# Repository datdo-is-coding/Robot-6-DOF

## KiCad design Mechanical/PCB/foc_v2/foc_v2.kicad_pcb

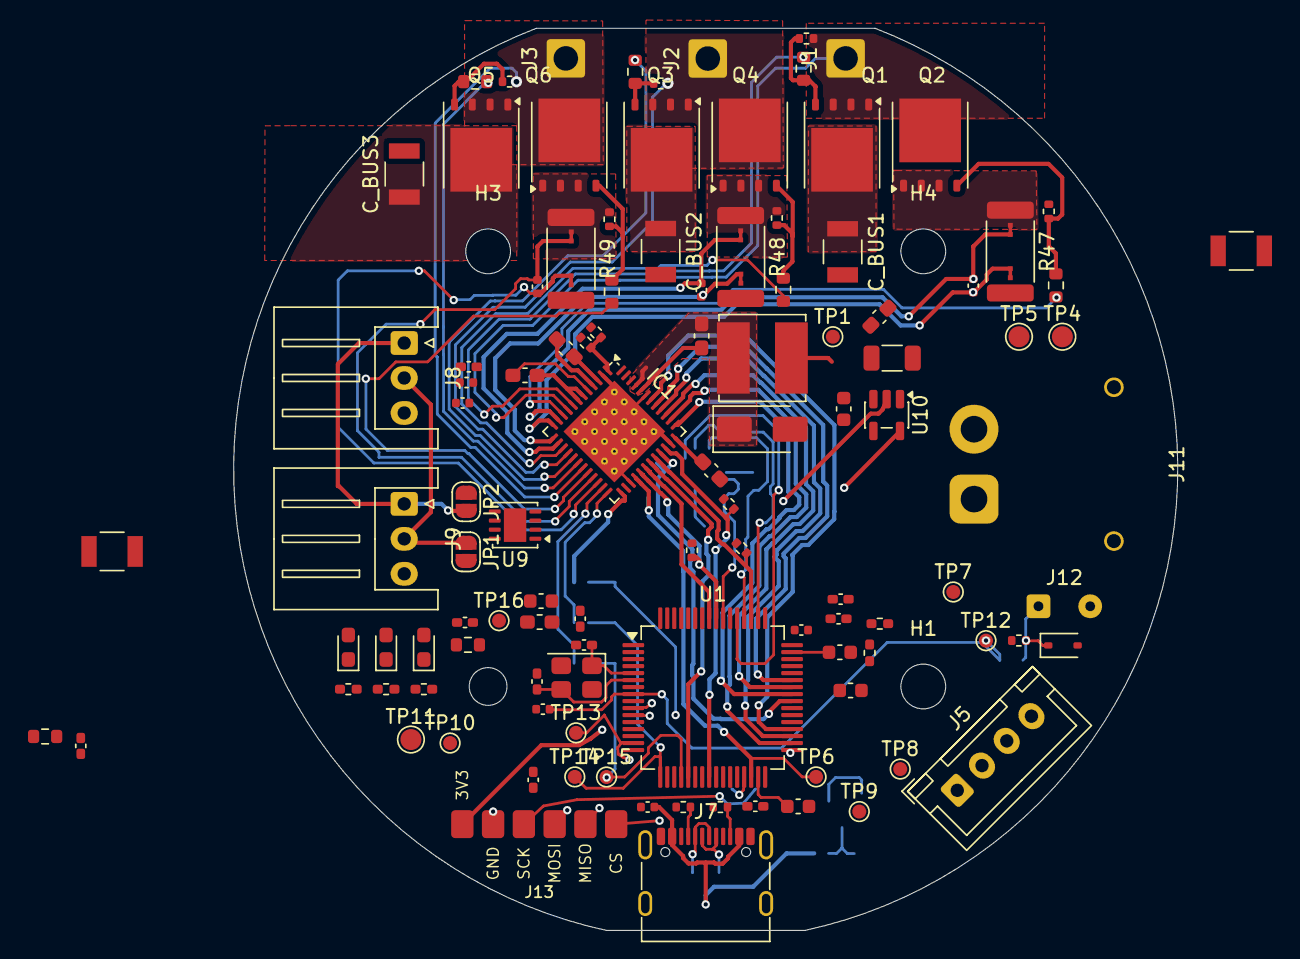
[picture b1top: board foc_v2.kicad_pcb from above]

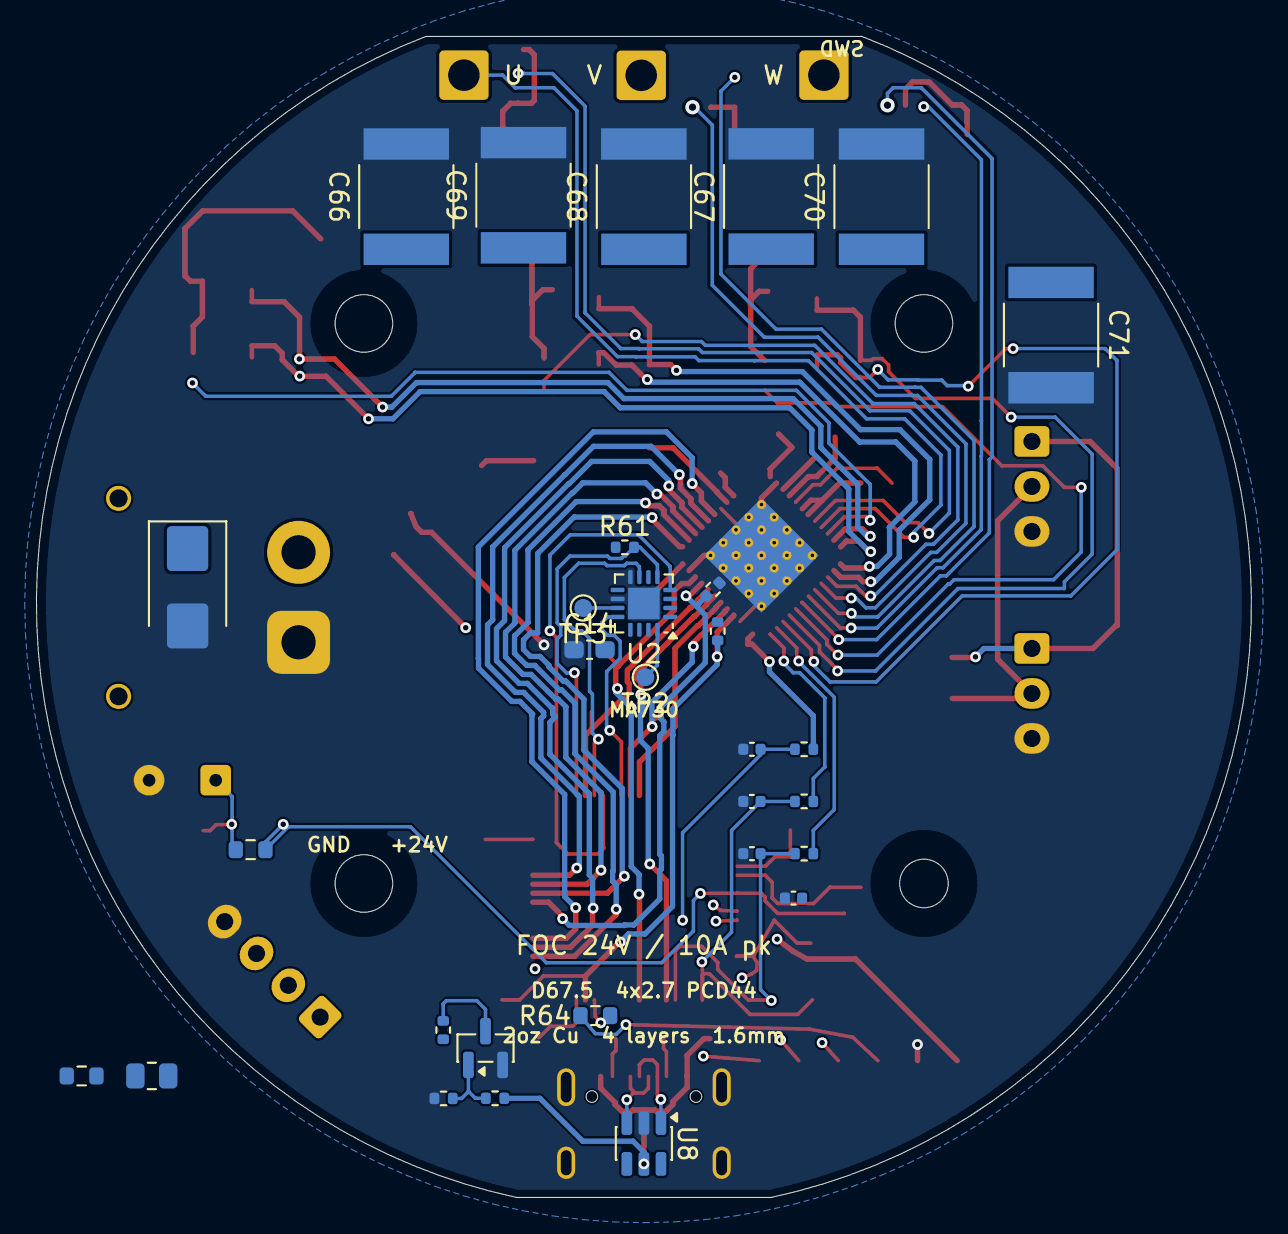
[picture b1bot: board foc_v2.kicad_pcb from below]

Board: 4 copper layers, 67.5 x 64.5 mm, 148 parts (30 on the bottom side), 98 nets.

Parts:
C1, C2, C3, C54, C55, C56: 1nF; C_0402_1005Metric
C4, C5, C7, C21, C50, C51, C52: 100nF; C_0402_1005Metric_Pad0.74x0.62mm_HandSolder
C6: 1uF; C_0402_1005Metric_Pad0.74x0.62mm_HandSolder
C8, C9: 33pF; C_0402_1005Metric_Pad0.74x0.62mm_HandSolder
C10, C11: 2.2uF; C_0603_1608Metric
C12, C17: 10uF; C_TDK_CGA6_SoftTerm_1210
C13, C15: 0.1uF; C_0603_1608Metric_Pad1.08x0.95mm_HandSolder
C14, C18, C20: 1uF; C_0603_1608Metric_Pad1.08x0.95mm_HandSolder
C16: 22uF; C_1206_3216Metric
C19: 47nF; C_0603_1608Metric_Pad1.08x0.95mm_HandSolder
C53, C59, C60, C61, C65: 100nF; C_0402_1005Metric
C57: 1uF; C_0603_1608Metric
C58: 4.7uF; C_0603_1608Metric
C62: 4.7nF; C_0603_1608Metric
C64: 10nF; C_0402_1005Metric
C66, C67, C68, C69, C70, C71: 22uF; C_TDK_CKG57N_6.0x5.0mm
C_BUS1, C_BUS2, C_BUS3: 10uF; C_TDK_CGA6_SoftTerm_1210
D1, D2: LED RED; LED_0603_1608Metric_Pad1.05x0.95mm_HandSolder
D3: LED GREEN; LED_0603_1608Metric_Pad1.05x0.95mm_HandSolder
D4: SS16; D_SMA
D6: SMBJ30A; D_SMB
D7: PESD3V3U1UA; D_SOD-323
FB1: 600R@100MHz; L_0603_1608Metric_Pad1.05x0.95mm_HandSolder
H1, H3, H4: MountingHole; MountingHole_3.2mm_M3
H2: MountingHole; MountingHole_2.7mm_M2.5
IC1: DRV8323RSRGZR; Texas_RGZ0048A_VQFN-48-1EP_7x7mm_P0.5mm_EP5.15x5.15mm_Therm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
J1: PHASE_U; SolderWire-1sqmm_1x01_D1.4mm_OD2.7mm
J2: PHASE_V; SolderWire-1sqmm_1x01_D1.4mm_OD2.7mm
J3: PHASE_W; SolderWire-1sqmm_1x01_D1.4mm_OD2.7mm
J5: Debug; JST_XH_B4B-XH-A_1x04_P2.50mm_Vertical
J7: USB_C_Receptacle_USB2.0_16P; USB_C_Receptacle_G-Switch_GT-USB-7010ASV
J8: CAN1; JST_XH_S3B-XH-A_1x03_P2.50mm_Horizontal
J9: CAN2; JST_XH_S3B-XH-A_1x03_P2.50mm_Horizontal
J11: 24V_IN; AMASS_XT30PW-M_Edge_NoSilk
J12: MOTOR_NTC; SolderWire-0.127sqmm_1x02_P3.7mm_D0.48mm_OD1mm
J13: ENC2; Encoder_SPI_SolderPads_1x06_P2.20mm
JP1: TERM_L; SolderJumper-2_P1.3mm_Open_RoundedPad1.0x1.5mm
JP2: TERM_H; SolderJumper-2_P1.3mm_Open_RoundedPad1.0x1.5mm
L1: 22uH; L_Bourns_SRN6045TA
NT1: KELVIN_CSA_SPA; NetTie_Kelvin
NT2: KELVIN_SNA; NetTie_Kelvin
NT3: KELVIN_CSA_SPB; NetTie_Kelvin
NT4: KELVIN_SNB; NetTie_Kelvin
NT5: KELVIN_CSA_SPC; NetTie_Kelvin
NT6: KELVIN_SNC; NetTie_Kelvin
Q1, Q2, Q3, Q4, Q5, Q6: CSD18532Q5B; TDSON-8-1
Q7: 2N7002; SOT-23
R1, R2, R3, R4, R5, R7: 2.2R; R_0603_1608Metric
R6: 18k; R_0402_1005Metric
R8, R42, R43, R52, R61, R62: 10k; R_0402_1005Metric
R9: 3k3; R_0402_1005Metric
R10, R50, R55, R56, R57, R58, R59, R60: 100k; R_0402_1005Metric
R32, R34: 10k; R_0402_1005Metric_Pad0.72x0.64mm_HandSolder
R33, R35, R36: 1k; R_0402_1005Metric_Pad0.72x0.64mm_HandSolder
R37, R38, R39: 100R; R_0402_1005Metric
R40, R41: 5.1k; R_0402_1005Metric
R44: 1M; R_0402_1005Metric
R45, R46: 60.4R; R_0603_1608Metric
R47, R48, R49: 5m; R_2512_6332Metric
R51: 4.7k; R_0402_1005Metric
R53: 150k; R_0805_2012Metric
R54: 10k; R_0603_1608Metric
R63: 1k; R_0603_1608Metric
R64: 33R; R_0603_1608Metric
TP1: TestPoint; TestPoint_Pad_D1.0mm
TP2: MGH_TP; TestPoint_Pad_D1.0mm
TP3: MGL_TP; TestPoint_Pad_D1.0mm
TP4: VS_24V; TestPoint_Pad_D1.5mm
TP5: PGND; TestPoint_Pad_D1.5mm
TP6: nFAULT; TestPoint_Pad_D1.0mm
TP7: ENABLE; TestPoint_Pad_D1.0mm
TP8: PV_SENSE; TestPoint_Pad_D1.0mm
TP9: +3V3; TestPoint_Pad_D1.0mm
TP10: +3V3A; TestPoint_Pad_D1.0mm
TP11: GND; TestPoint_Pad_D1.5mm
TP12: MOTOR_TEMP_ADC; TestPoint_Pad_D1.0mm
TP13: ADC_IA; TestPoint_Pad_D1.0mm
TP14: ADC_IB; TestPoint_Pad_D1.0mm
TP15: ADC_IC; TestPoint_Pad_D1.0mm
TP16: NRST; TestPoint_Pad_D1.0mm
U1: STM32F405RGTx; LQFP-64_10x10mm_P0.5mm
U2: MA730; MA730_QFN16_3x3
U8: USBLC6-2SC6; SOT-23-6
U9: TJA1051TK-3; HVSON-8-1EP_3x3mm_P0.65mm_EP1.6x2.4mm
U10: AP2112K-3.3; SOT-23-5
Y1: 12MHz; Crystal_SMD_3225-4Pin_3.2x2.5mm

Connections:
+3V3: C4.1, C14.2, C21.2, C50.1, C51.1, C52.1, C53.1, C58.1, C60.1, FB1.2, IC1.26 (VREF), J5.1, J13.1, R8.1, R32.1, R33.1, R35.1, R36.1, R42.1, R51.1, R52.1, R61.1, TP9.1 (1_1), U1.1 (VBAT), U1.19 (VDD), U1.32 (VDD), U1.48 (VDD), U1.64 (VDD), U2.13 (VDD), U9.5 (VIO), U10.5 (VOUT)
+3V3A: C5.1, C6.1, FB1.1, R62.1, TP10.1 (1_1), U1.13 (VDDA)
+5V: C16.1, C57.1, C61.1, L1.1, R6.1, TP1.1 (1_1), U9.3 (VCC), U10.1 (VIN), U10.3 (EN)
/COMMUNICATION/CAN_H: J8.1, J9.1, JP2.2 (B), U9.7 (CANH)
/COMMUNICATION/CAN_L: J8.2, J9.2, JP1.1 (A), U9.6 (CANL)
/COMMUNICATION/CAN_RX: U1.61 (PB8), U9.4 (RXD)
/COMMUNICATION/CAN_TX: U1.62 (PB9), U9.1 (TXD)
/COMMUNICATION/CC1: J7.A5 (CC1), R40.1
/COMMUNICATION/CC2: J7.B5 (CC2), R41.1
/COMMUNICATION/USB_DM_CONN: J7.A7 (D-), J7.B7 (D-), U8.1 (I/O1)
/COMMUNICATION/USB_DP_CONN: J7.A6 (D+), J7.B6 (D+), U8.3 (I/O2)
/COMMUNICATION/USB_N: U1.44 (PA11), U8.6 (I/O1)
/COMMUNICATION/USB_P: U1.45 (PA12), U8.4 (I/O2)
/COMMUNICATION/USB_VBUS: Q7.3 (D), R42.2, U1.14 (PA0)
/COMMUNICATION/VBUS: C59.1, J7.A4 (VBUS), J7.A9 (VBUS), J7.B4 (VBUS), J7.B9 (VBUS), R43.1, U8.5 (VBUS)
/COMMUNICATION/VBUS_GATE: Q7.1 (G), R43.2, R44.1
/GATE_DRV/CSA_CAL1: IC1.34 (CAL), R50.1, U1.24 (PC4)
/GATE_DRV/CSA_SPA: C1.1, IC1.11 (SPA), NT1.1
/GATE_DRV/CSA_SPB: C2.1, IC1.14 (SPB), NT3.1
/GATE_DRV/CSA_SPC: C3.1, IC1.21 (SPC), NT5.1
/GATE_DRV/EN_GATE1: IC1.33 (ENABLE), R10.1, TP7.1 (1_1), U1.40 (PC9)
/GATE_DRV/GHA: IC1.8 (GHA), R1.1
/GATE_DRV/GHB: IC1.17 (GHB), R3.1
/GATE_DRV/GHC: IC1.18 (GHC), R5.1
/GATE_DRV/GLA: IC1.10 (GLA), R2.1
/GATE_DRV/GLB: IC1.15 (GLB), R4.1
/GATE_DRV/GLC: IC1.20 (GLC), R7.1
/GATE_DRV/ISENSE1_A: IC1.25 (SOA), R37.1
/GATE_DRV/ISENSE1_B: IC1.24 (SOB), R38.1
/GATE_DRV/ISENSE1_C: IC1.23 (SOC), R39.1
/GATE_DRV/NFAULT1: IC1.28 (NFAULT), R8.2, TP6.1 (1_1), U1.30 (PB11)
/GATE_DRV/PV_SENSE: C64.1, R53.2, R54.1, TP8.1 (1_1), U1.22 (PA6)
/GATE_DRV/PWM1_A: IC1.37 (INHA), U1.41 (PA8)
/GATE_DRV/PWM1_AN: IC1.38 (INLA), U1.34 (PB13)
/GATE_DRV/PWM1_B: IC1.39 (INHB), U1.42 (PA9)
/GATE_DRV/PWM1_BN: IC1.40 (INLB), U1.35 (PB14)
/GATE_DRV/PWM1_C: IC1.41 (INHC), U1.43 (PA10)
/GATE_DRV/PWM1_CN: IC1.42 (INLC), U1.36 (PB15)
/GATE_DRV/SHA: IC1.9 (SHA), J1.1 (1_1), Q1.1 (S), Q1.2 (S), Q1.3 (S), Q2.5 (D), R55.2
/GATE_DRV/SHB: IC1.16 (SHB), J2.1 (1_1), Q3.1 (S), Q3.2 (S), Q3.3 (S), Q4.5 (D), R57.2
/GATE_DRV/SHC: IC1.19 (SHC), J3.1 (1_1), Q5.1 (S), Q5.2 (S), Q5.3 (S), Q6.5 (D), R59.2
/GATE_DRV/SNA: C1.2, IC1.12 (SNA), NT2.1
/GATE_DRV/SNB: C2.2, IC1.13 (SNB), NT4.1
/GATE_DRV/SNC: C3.2, IC1.22 (SNC), NT6.1
/GATE_DRV/SPA: NT1.2, Q2.1 (S), Q2.2 (S), Q2.3 (S), R47.1, R56.2
/GATE_DRV/SPB: NT3.2, Q4.1 (S), Q4.2 (S), Q4.3 (S), R48.1, R58.2
/GATE_DRV/SPC: NT5.2, Q6.1 (S), Q6.2 (S), Q6.3 (S), R49.1, R60.2
/GATE_DRV/SPI1_MISO: IC1.29 (SDO), R51.2, U1.56 (PB4)
/GATE_DRV/SPI1_MOSI: IC1.30 (SDI), U1.57 (PB5)
/GATE_DRV/SPI1_SCK: IC1.31 (SCLK), U1.21 (PA5)
/GATE_DRV/SPI1_SS0: IC1.32 (NSCS), R52.2, U1.51 (PC10)
/HALL/HALL_CS: R61.2, U1.50 (PA15), U2.5 (~CS)
/HALL/HALL_MISO: U1.52 (PC11), U2.7 (MISO)
/HALL/HALL_MOSI: U1.53 (PC12), U2.4 (MOSI)
/HALL/HALL_SCLK: U1.55 (PB3), U2.12 (SCLK)
/MCU/ADC_IA: C54.1, R37.2, TP13.1 (1_1), U1.15 (PA1)
/MCU/ADC_IB: C55.1, R38.2, TP14.1 (1_1), U1.17 (PA3)
/MCU/ADC_IC: C56.1, R39.2, TP15.1 (1_1), U1.20 (PA4)
/MCU/BOOT0: R34.2, U1.60 (BOOT0)
/MCU/ENC2_CS: J13.6, U1.33 (PB12)
/MCU/ENC2_SCK: J13.3, R64.2
/MCU/LED_G: D3.1 (K), U1.3 (PC14)
/MCU/LED_R: D2.1 (K), U1.2 (PC13)
/MCU/MOTOR_TEMP_ADC: C65.1, R63.1, TP12.1 (1_1), U1.8 (PC0)
/MCU/NRST: C7.1, R32.2, TP16.1 (1_1), U1.7 (NRST)
/MCU/OSC_IN: C8.2, U1.5 (PH0), Y1.1
/MCU/OSC_OUT: C9.2, U1.6 (PH1), Y1.3
/MCU/SPI2_MISO: J13.5, U1.10 (PC2)
/MCU/SPI2_MOSI: J13.4, U1.11 (PC3)
/MCU/SPI2_SCK: R64.1, U1.29 (PB10)
/MCU/SWCLK: J5.3, U1.49 (PA14)
/MCU/SWDIO: J5.2, U1.46 (PA13)
DVDD: C20.1, IC1.36 (DVDD)
GND: C4.2, C5.2, C6.2, C7.2, C8.1, C9.1, C10.2, C11.2, C12.2, C13.2, C14.1, C16.2, C17.1, C20.2, C21.1, C50.2, C51.2, C52.2, C53.2, C54.2, C55.2, C56.2, C57.2, C58.2, C59.2, C60.2, C61.2, C62.2, C64.2, C65.2, C66.2, C67.2, C68.2, C69.2, C70.2, C71.2, C_BUS1.2, C_BUS2.2, C_BUS3.2, D1.1 (K), D4.2 (A), D6.2 (A), D7.2 (A), IC1.2 (PGND), IC1.27 (DGND), IC1.35 (AGND), IC1.43 (BGND), IC1.49 (THERMAL_PAD), J5.4, J7.A1 (GND), J7.A12 (GND), J7.B1 (GND), J7.B12 (GND), J7.SH (SHIELD), J8.3, J9.3, J11.1, J12.2, J13.2, NT2.2, NT4.2, NT6.2, Q7.2 (S), R9.2, R10.2, R34.1, R40.2, R41.2, R44.2, R47.2, R48.2, R49.2, R50.2, R54.2, TP5.1 (1_1), TP11.1 (1_1), U1.12 (VSSA), U1.18 (VSS), U1.63 (VSS), U2.8 (GND), U2.10 (TEST), U2.17 (PAD), U8.2 (GND), U9.2 (GND), U9.8 (S), U9.9 (GND), U10.2 (GND), Y1.2 (G), Y1.4 (G)
unnamed: C62.1, R45.2, R46.1
unnamed: D1.2 (A), R33.2
unnamed: D2.2 (A), R35.2
unnamed: D3.2 (A), R36.2
unnamed: C15.1, D4.1 (K), IC1.45 (SW), L1.2
unnamed: D7.1 (K), J12.1, R62.2, R63.2
unnamed: C15.2, IC1.44 (CB)
unnamed: C19.1, IC1.4 (CPH)
unnamed: C19.2, IC1.3 (CPL)
unnamed: IC1.1 (FB), R6.2, R9.1
unnamed: C18.1, IC1.5 (VCP)
unnamed: JP1.2 (B), R46.2
unnamed: JP2.1 (A), R45.1
unnamed: Q1.4 (G), R1.2, R55.1
unnamed: Q2.4 (G), R2.2, R56.1
unnamed: Q3.4 (G), R3.2, R57.1
unnamed: Q4.4 (G), R4.2, R58.1
unnamed: Q5.4 (G), R5.2, R59.1
unnamed: Q6.4 (G), R7.2, R60.1
unnamed: C10.1, U1.31 (VCAP_1)
unnamed: C11.1, U1.47 (VCAP_2)
unnamed: TP2.1 (1_1), U2.16 (MGH)
unnamed: TP3.1 (1_1), U2.11 (MGL)
VS: C12.1, C13.1, C17.2, C18.2, C66.1, C67.1, C68.1, C69.1, C70.1, C71.1, C_BUS1.1, C_BUS2.1, C_BUS3.1, D6.1 (K), IC1.6 (VM), IC1.7 (VDRAIN), IC1.47 (VIN), IC1.48 (NSHDN), J11.2, Q1.5 (D), Q3.5 (D), Q5.5 (D), R53.1, TP4.1 (1_1)

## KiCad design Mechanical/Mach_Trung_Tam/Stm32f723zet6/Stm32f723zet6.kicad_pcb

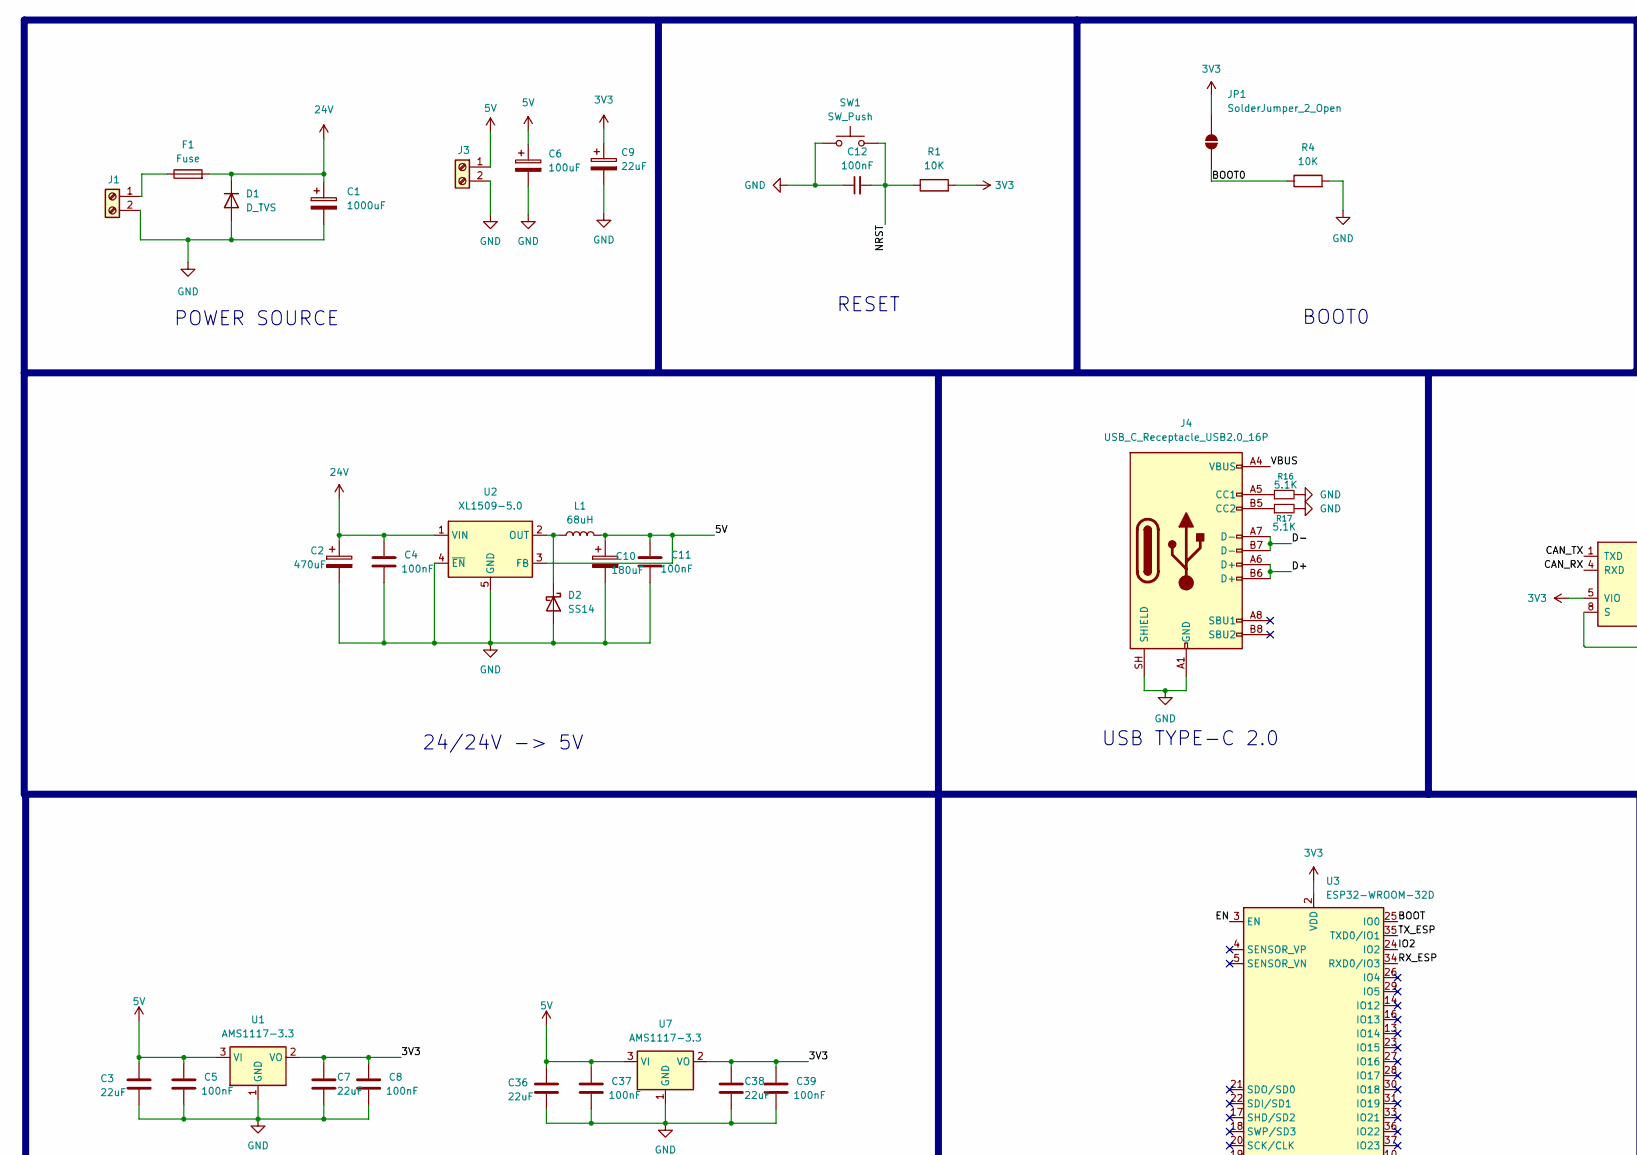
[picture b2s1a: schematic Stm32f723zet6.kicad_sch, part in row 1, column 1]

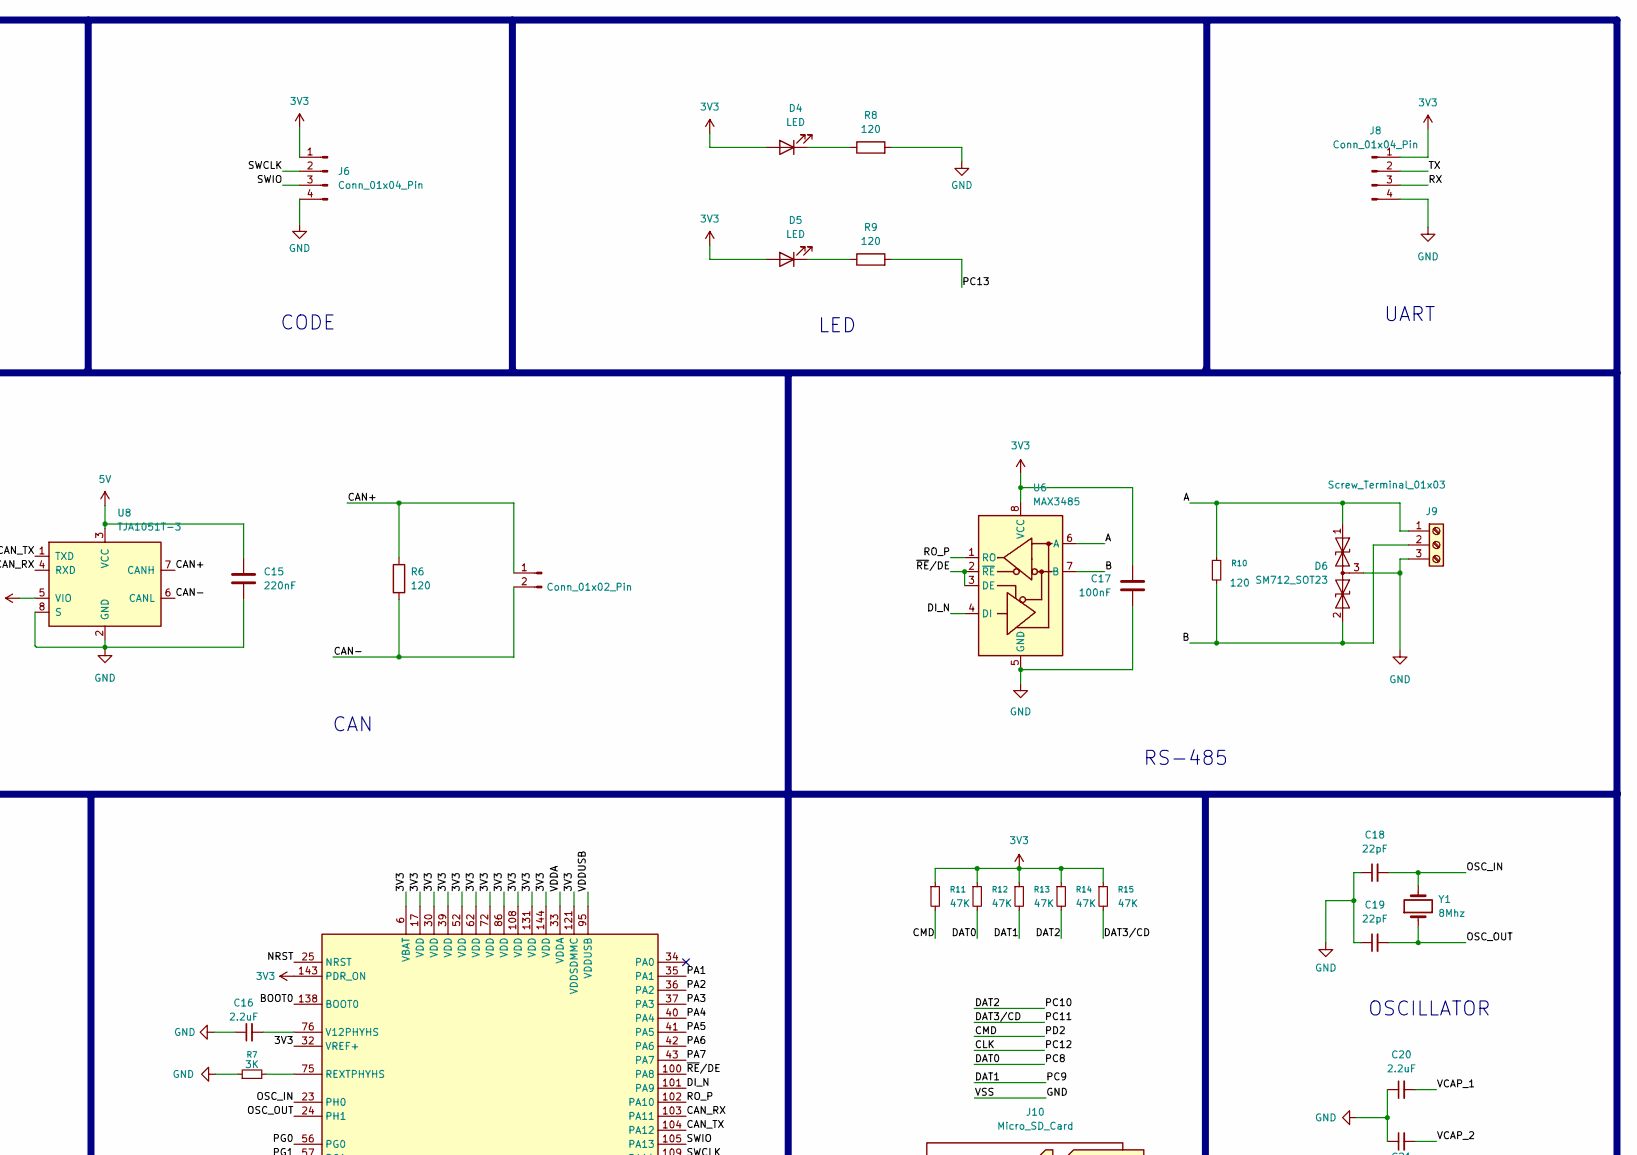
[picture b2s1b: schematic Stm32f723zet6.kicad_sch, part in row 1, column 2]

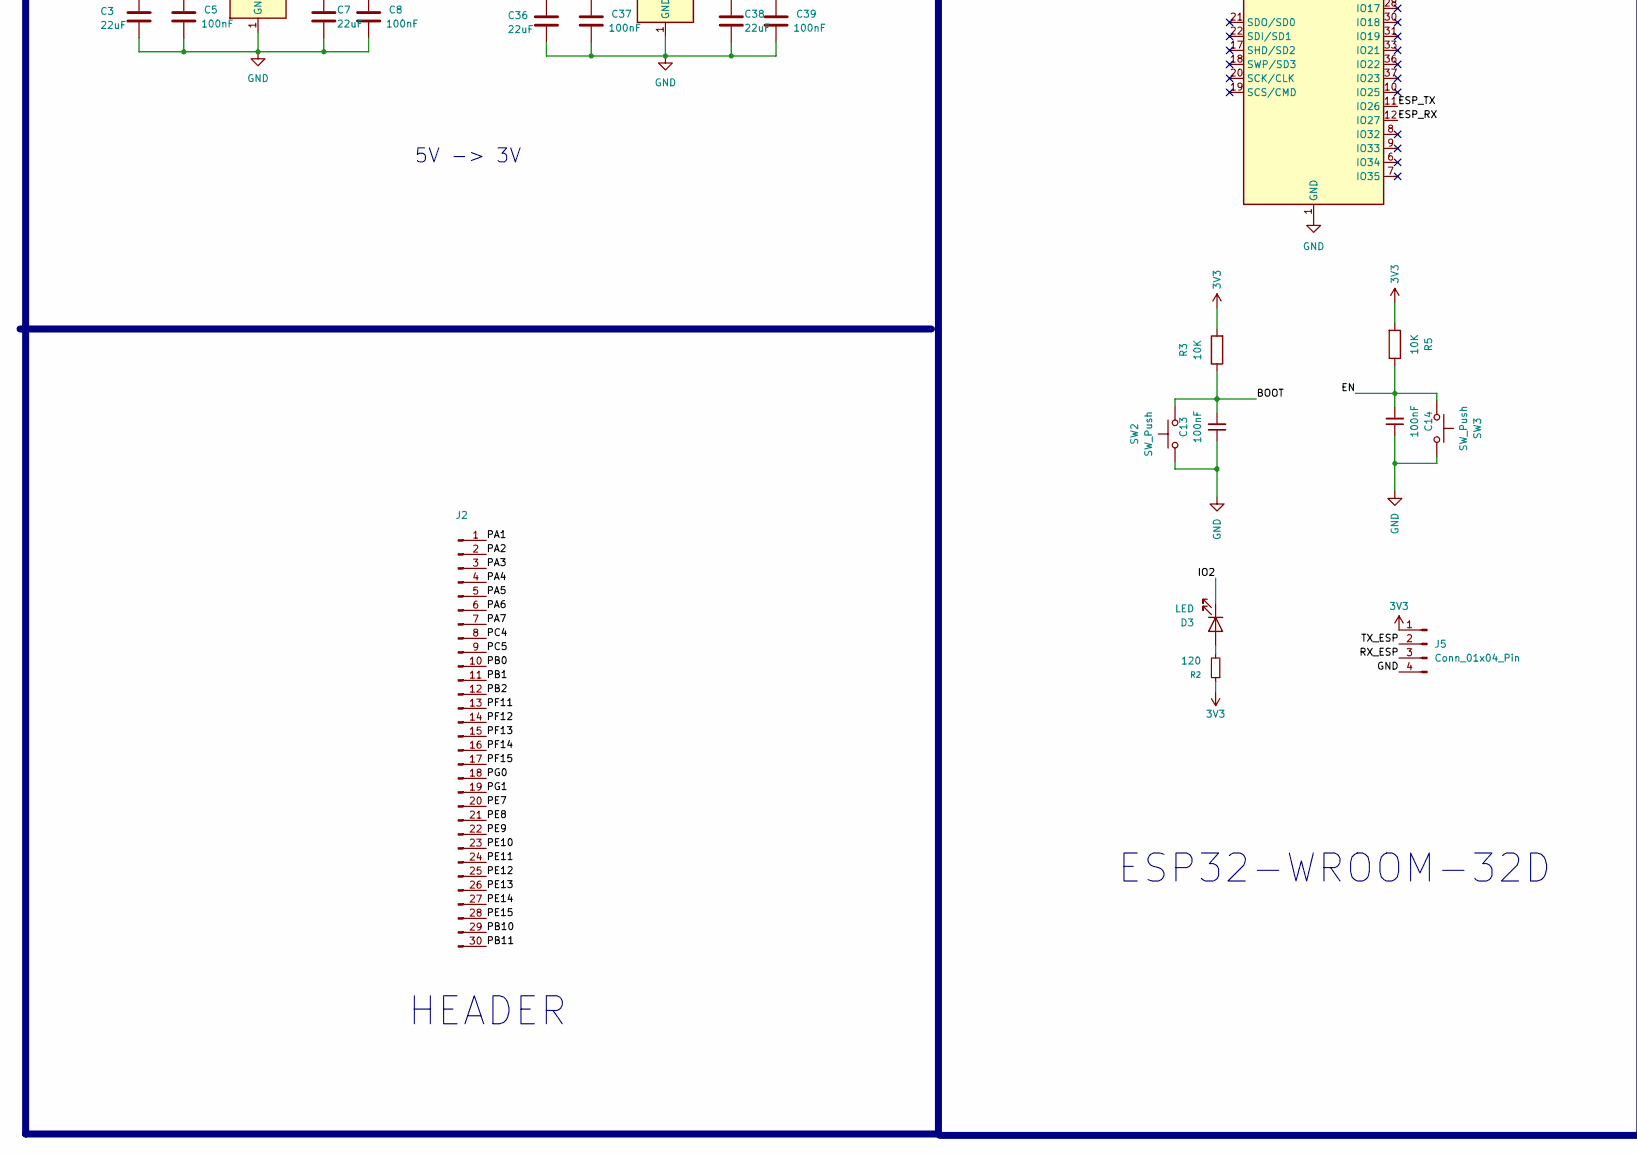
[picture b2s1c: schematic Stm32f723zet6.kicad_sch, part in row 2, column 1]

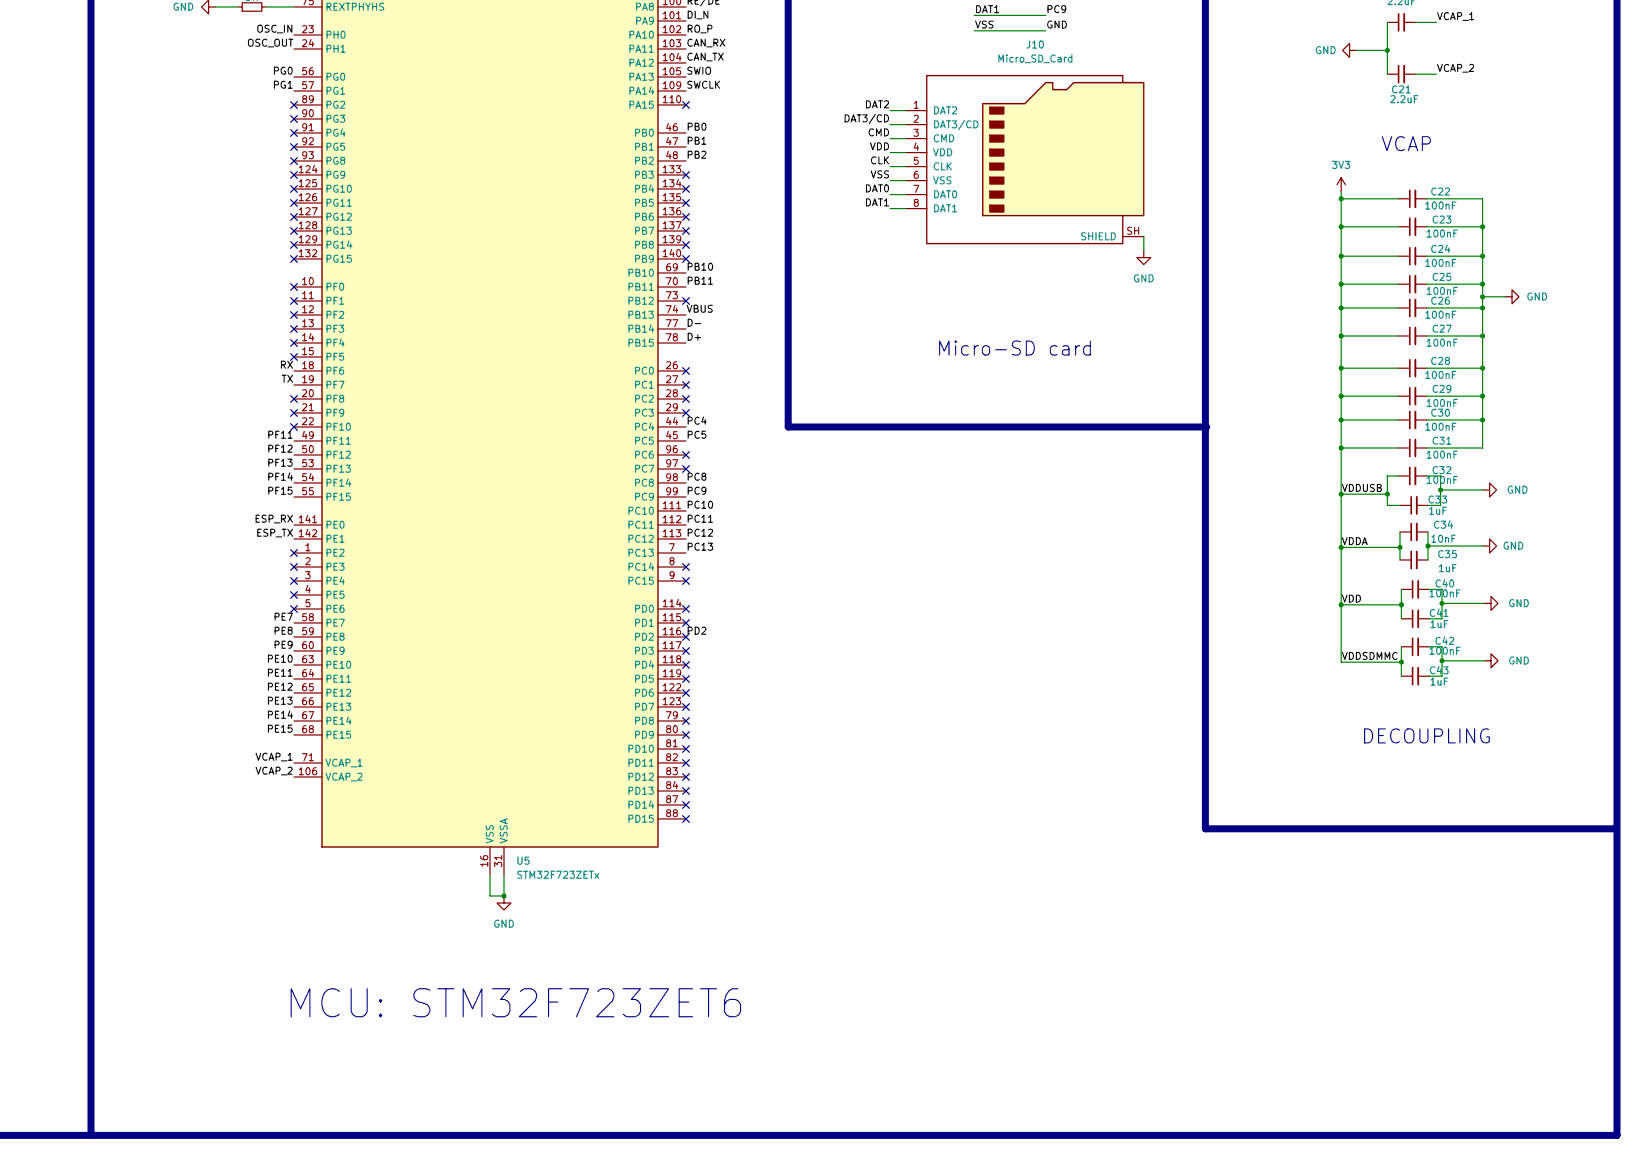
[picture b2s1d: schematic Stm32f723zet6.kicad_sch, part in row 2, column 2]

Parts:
C1: 1000uF; CP_Elec_10x10.5
C2: 470uF; CP_Elec_8x10.5
C3, C7, C36, C38: 22uF; C_0805_2012Metric_Pad1.18x1.45mm_HandSolder
C4, C5, C8, C11, C12, C13, C14, C17, C22, C23, C24, C25, C26, C27, C28, C29, C30, C31, C32, C37, C39, C40, C42: 100nF; C_0805_2012Metric_Pad1.18x1.45mm_HandSolder
C6: 100uF; CP_Elec_6.3x5.4
C9: 22uF; CP_Elec_4x5.4
C10: 180uF; CP_Elec_8x10
C15: 220nF; C_0805_2012Metric_Pad1.18x1.45mm_HandSolder
C16, C20, C21: 2.2uF; C_0805_2012Metric_Pad1.18x1.45mm_HandSolder
C18, C19: 22pF; C_0805_2012Metric_Pad1.18x1.45mm_HandSolder
C33, C35, C41, C43: 1uF; C_0805_2012Metric_Pad1.18x1.45mm_HandSolder
C34: 10nF; C_0805_2012Metric_Pad1.18x1.45mm_HandSolder
D1: D_TVS; D_SMB_Handsoldering
D2: SS14; D_SMA
D3, D4, D5: LED; LED_0805_2012Metric_Pad1.15x1.40mm_HandSolder
D6: SM712_SOT23; SOT-23
F1: Fuse; Fuse_1206_3216Metric
J1: Screw_Terminal_01x02; TerminalBlock_Phoenix_MKDS-1,5-2-5.08_1x02_P5.08mm_Horizont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
J2: Conn_01x30_Pin; PinHeader_1x30_P2.54mm_Vertical
J3: Screw_Terminal_01x02; TerminalBlock_Phoenix_PT-1,5-2-3.5-H_1x02_P3.50mm_Horizontal
J4: USB_C_Receptacle_USB2.0_16P; USB_C_Receptacle_GCT_USB4105-xx-A_16P_TopMnt_Horizontal
J5, J6, J8: Conn_01x04_Pin; PinHeader_1x04_P2.54mm_Vertical
J7: Conn_01x02_Pin; PinHeader_1x02_P2.54mm_Vertical
J9: Screw_Terminal_01x03; TerminalBlock_Phoenix_PT-1,5-3-3.5-H_1x03_P3.50mm_Horizontal
J10: Micro_SD_Card; microSD_HC_Molex_47219-2001
JP1: SolderJumper_2_Open; SolderJumper-2_P1.3mm_Open_Pad1.0x1.5mm
L1: 68uH; L_0805_2012Metric_Pad1.05x1.20mm_HandSolder
R1, R3, R4, R5: 10K; R_0805_2012Metric_Pad1.20x1.40mm_HandSolder
R2, R6, R8, R9, R10: 120; R_0805_2012Metric_Pad1.20x1.40mm_HandSolder
R7: 3K; R_0805_2012Metric_Pad1.20x1.40mm_HandSolder
R11, R12, R13, R14, R15: 47K; R_0805_2012Metric_Pad1.20x1.40mm_HandSolder
R16, R17: 5.1K; R_0805_2012Metric_Pad1.20x1.40mm_HandSolder
SW1, SW2, SW3: SW_Push; SW_Tactile_SPST_NO_Straight_CK_PTS636Sx25SMTRLFS
U1, U7: AMS1117-3.3; SOT-223-3_TabPin2
U2: XL1509-5.0; SOIC-8_3.9x4.9mm_P1.27mm
U3: ESP32-WROOM-32D
U5: STM32F723ZETx; LQFP-144_20x20mm_P0.5mm
U6: MAX3485; SOIC-8_3.9x4.9mm_P1.27mm
U8: TJA1051T-3; SOIC-8_3.9x4.9mm_P1.27mm
Y1: 8Mhz; Crystal_SMD_5032-2Pin_5.0x3.2mm_HandSoldering

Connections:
3V3: C7.1, C8.1, C9.1, C17.2, C22.1, C23.1, C24.1, C25.1, C26.1, C27.1, C28.1, C29.1, C30.1, C31.1, C32.1, C33.1, C34.1, C35.1, C38.1, C39.1, C40.1, C41.1, C42.1, C43.1, D4.2 (A), D5.2 (A), J5.1, J6.1, J8.1, J10.4 (VDD), JP1.2 (B), R1.2, R2.1, R3.2, R5.2, R11.1, R12.1, R13.1, R14.1, R15.1, U1.2 (VO), U3.2 (VDD), U5.6 (VBAT), U5.17 (VDD), U5.30 (VDD), U5.32 (VREF+), U5.33 (VDDA), U5.39 (VDD), U5.52 (VDD), U5.62 (VDD), U5.72 (VDD), U5.86 (VDD), U5.95 (VDDUSB), U5.108 (VDD), U5.121 (VDDSDMMC), U5.131 (VDD), U5.143 (PDR_ON), U5.144 (VDD), U6.8 (VCC), U7.2 (VO), U8.5 (VIO)
5V: C3.1, C5.1, C6.1, C10.1, C11.1, C15.1, C36.1, C37.1, J3.1, L1.2, U1.3 (VI), U2.3 (FB), U7.3 (VI), U8.3 (VCC)
24V: C1.1, C2.1, C4.1, D1.1 (K), F1.2, U2.1 (VIN)
/A: D6.1 (A1), J9.1, R10.1, U6.6 (A)
/B: D6.2 (A2), J9.2, R10.2, U6.7 (B)
/BOOT: C13.2, R3.1, SW2.2, U3.25 (IO0)
/BOOT0: JP1.1 (A), R4.1, U5.138 (BOOT0)
/CAN+: J7.1, R6.1, U8.7 (CANH)
/CAN-: J7.2, R6.2, U8.6 (CANL)
/CAN_RX: U5.103 (PA11), U8.4 (RXD)
/CAN_TX: U5.104 (PA12), U8.1 (TXD)
/CLK: J10.5 (CLK), U5.113 (PC12)
/CMD: J10.3 (CMD), R11.2, U5.116 (PD2)
/D+: J4.A6 (D+), J4.B6 (D+), U5.78 (PB15)
/D-: J4.A7 (D-), J4.B7 (D-), U5.77 (PB14)
/DAT0: J10.7 (DAT0), R12.2, U5.98 (PC8)
/DAT1: J10.8 (DAT1), R13.2, U5.99 (PC9)
/DAT2: J10.1 (DAT2), R14.2, U5.111 (PC10)
/DAT3/CD: J10.2 (DAT3/CD), R15.2, U5.112 (PC11)
/DI_N: U5.101 (PA9), U6.4 (DI)
/EN: C14.2, R5.1, SW3.2, U3.3 (EN)
/ESP_RX: U3.12 (IO27), U5.141 (PE0)
/ESP_TX: U3.11 (IO26), U5.142 (PE1)
/IO2: D3.1 (K), U3.24 (IO2)
/NRST: C12.2, R1.1, SW1.2, U5.25 (NRST)
/OSC_IN: C18.2, U5.23 (PH0), Y1.2
/OSC_OUT: C19.2, U5.24 (PH1), Y1.1
/PA1: J2.1, U5.35 (PA1)
/PA2: J2.2, U5.36 (PA2)
/PA3: J2.3, U5.37 (PA3)
/PA4: J2.4, U5.40 (PA4)
/PA5: J2.5, U5.41 (PA5)
/PA6: J2.6, U5.42 (PA6)
/PA7: J2.7, U5.43 (PA7)
/PB0: J2.10, U5.46 (PB0)
/PB1: J2.11, U5.47 (PB1)
/PB2: J2.12, U5.48 (PB2)
/PB10: J2.29, U5.69 (PB10)
/PB11: J2.30, U5.70 (PB11)
/PC4: J2.8, U5.44 (PC4)
/PC5: J2.9, U5.45 (PC5)
/PC13: R9.2, U5.7 (PC13)
/PE7: J2.20, U5.58 (PE7)
/PE8: J2.21, U5.59 (PE8)
/PE9: J2.22, U5.60 (PE9)
/PE10: J2.23, U5.63 (PE10)
/PE11: J2.24, U5.64 (PE11)
/PE12: J2.25, U5.65 (PE12)
/PE13: J2.26, U5.66 (PE13)
/PE14: J2.27, U5.67 (PE14)
/PE15: J2.28, U5.68 (PE15)
/PF11: J2.13, U5.49 (PF11)
/PF12: J2.14, U5.50 (PF12)
/PF13: J2.15, U5.53 (PF13)
/PF14: J2.16, U5.54 (PF14)
/PF15: J2.17, U5.55 (PF15)
/PG0: J2.18, U5.56 (PG0)
/PG1: J2.19, U5.57 (PG1)
/RO_P: U5.102 (PA10), U6.1 (RO)
/RX: J8.3, U5.18 (PF6)
/RX_ESP: J5.3, U3.34 (RXD0/IO3)
/SWCLK: J6.2, U5.109 (PA14)
/SWIO: J6.3, U5.105 (PA13)
/TX: J8.2, U5.19 (PF7)
/TX_ESP: J5.2, U3.35 (TXD0/IO1)
/VBUS: J4.A4 (VBUS), J4.A9 (VBUS), J4.B4 (VBUS), J4.B9 (VBUS), U5.74 (PB13)
/VCAP_1: C20.2, U5.71 (VCAP_1)
/VCAP_2: C21.2, U5.106 (VCAP_2)
/~RE/DE: U5.100 (PA8), U6.2 (~RE), U6.3 (DE)
GND: C1.2, C2.2, C3.2, C4.2, C5.2, C6.2, C7.2, C8.2, C9.2, C10.2, C11.2, C12.1, C13.1, C14.1, C15.2, C16.1, C17.1, C18.1, C19.1, C20.1, C21.1, C22.2, C23.2, C24.2, C25.2, C26.2, C27.2, C28.2, C29.2, C30.2, C31.2, C32.2, C33.2, C34.2, C35.2, C36.2, C37.2, C38.2, C39.2, C40.2, C41.2, C42.2, C43.2, D1.2 (A), D2.2 (A), D6.3 (common), J1.2, J3.2, J4.A1 (GND), J4.A12 (GND), J4.B1 (GND), J4.B12 (GND), J4.SH (SHIELD), J5.4, J6.4, J8.4, J9.3, J10.6 (VSS), J10.SH (SHIELD), R4.2, R7.1, R8.2, R16.2, R17.2, SW1.1, SW2.1, SW3.1, U1.1 (GND), U2.4 (~EN), U2.5 (GND), U2.6 (GND), U2.7 (GND), U2.8 (GND), U3.1 (GND), U3.15 (GND), U3.38 (GND), U3.39 (GND), U5.16 (VSS), U5.31 (VSSA), U5.38 (VSS), U5.51 (VSS), U5.61 (VSS), U5.85 (VSS), U5.94 (VSS), U5.107 (VSS), U5.120 (VSS), U5.130 (VSS), U6.5 (GND), U7.1 (GND), U8.2 (GND), U8.8 (S)
unnamed: D2.1 (K), L1.1, U2.2 (OUT)
unnamed: D3.2 (A), R2.2
unnamed: D4.1 (K), R8.1
unnamed: D5.1 (K), R9.1
unnamed: F1.1, J1.1
unnamed: J4.A5 (CC1), R16.1
unnamed: J4.B5 (CC2), R17.1
unnamed: R7.2, U5.75 (REXTPHYHS)
unnamed: C16.2, U5.76 (V12PHYHS)

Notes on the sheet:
5V -> 3V
VCAP
CODE
HEADER
POWER SOURCE
RESET
BOOT0
CAN
USB TYPE-C 2.0
Micro-SD card
MCU: STM32F723ZET6
24/24V -> 5V
LED
UART
OSCILLATOR
DECOUPLING
ESP32-WROOM-32D
RS-485

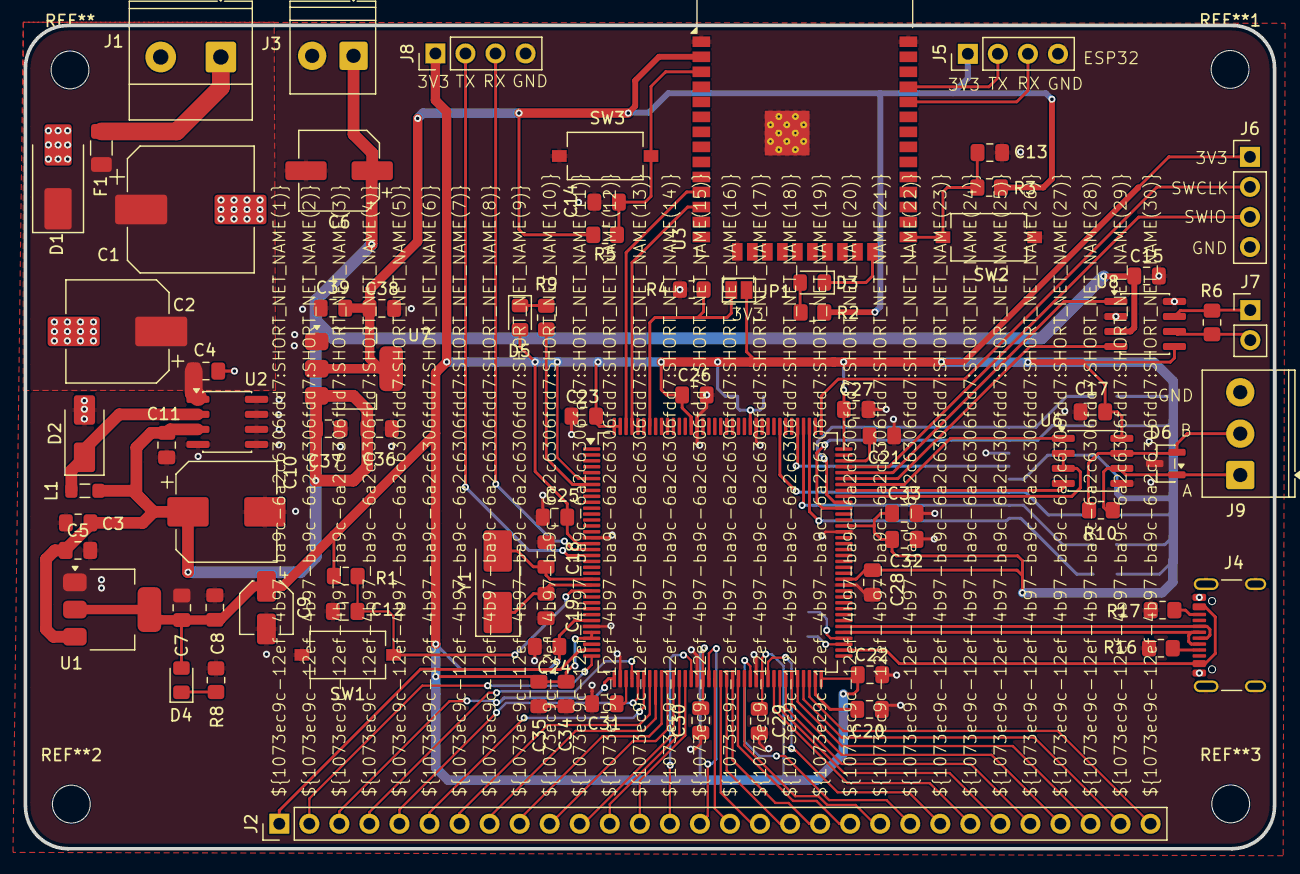
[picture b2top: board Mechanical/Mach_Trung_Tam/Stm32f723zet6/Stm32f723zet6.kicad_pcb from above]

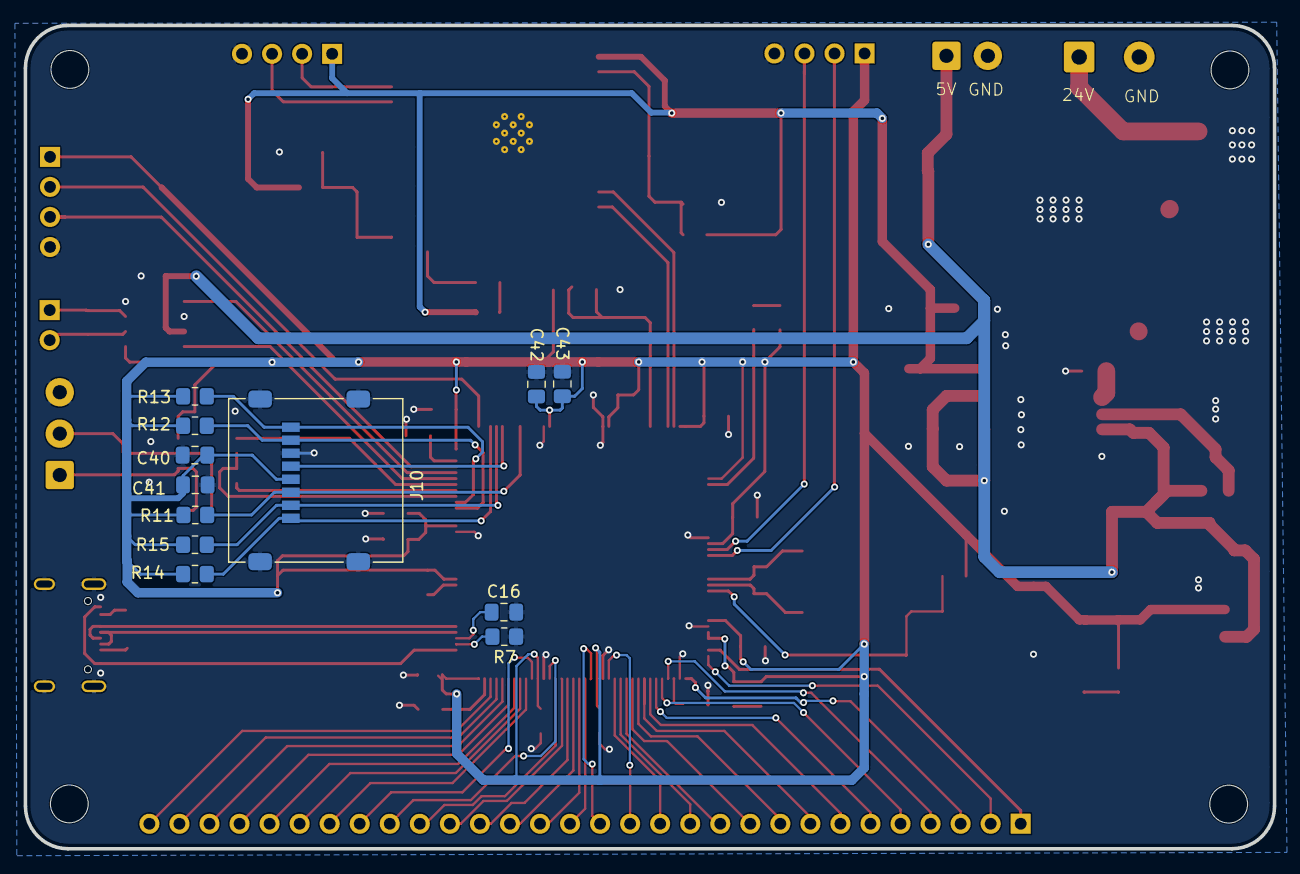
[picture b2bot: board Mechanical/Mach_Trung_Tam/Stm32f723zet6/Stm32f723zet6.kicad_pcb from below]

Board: 2 copper layers, 105.6 x 69.6 mm, 90 parts (12 on the bottom side), 79 nets.
